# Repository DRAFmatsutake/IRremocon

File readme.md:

# 汎用リモコン送受信機
# 機能
- web経由で任意信号の送信
- web経由で任意信号の受信＆送信用数値へ変換
# 仕様
- esp32 devkit V1 を使用
- arduinoIDEで作成
- IRセンサ関係を行えるIRremoteLibraryの使用
- 送信信号は4bitを文字化したものを使用する
# 回路
- 電源はUSB給電を想定
- トランジスタhfeは250前後とする
- 赤外線LEDへの給電は瞬間電流を超えない程度の150mA前後で設計

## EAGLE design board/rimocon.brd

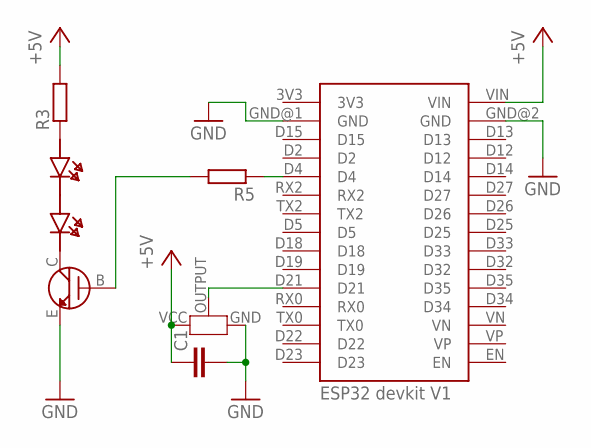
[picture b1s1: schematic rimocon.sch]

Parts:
C1: C-EU025-024X044; C025-024X044
R3, R5: R-EU_0204/5; 0204/5
U$1: 2SC1815; 1815
U$2: OSRB38C9AA; OSRB38
U$3: ESP32DEVKITV1
U$5, U$6: LEDOSI5FU3A11C; OSI5FU3A11C

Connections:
3V3: U$3.3V3
+5V: C1.1, R3.2, U$2.VCC, U$3.VIN
GND: C1.2, U$1.E, U$2.GND, U$3.GND@1 (GND), U$3.GND@2 (GND)
unnamed: U$1.C, U$5.K (CATHODE)
unnamed: R3.1, U$6.A (ANODE)
unnamed: R5.1, U$3.D4
unnamed: U$2.OUTPUT, U$3.D21
unnamed: R5.2, U$1.B
unnamed: U$5.A (ANODE), U$6.K (CATHODE)

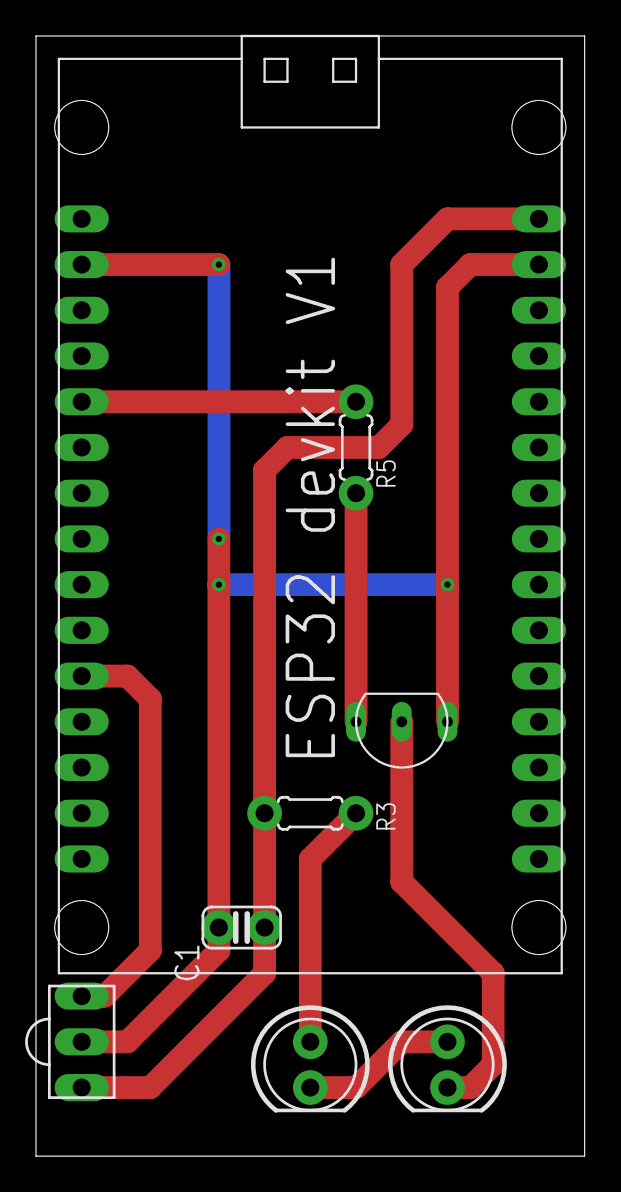
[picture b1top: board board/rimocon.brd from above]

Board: 2 copper layers, 30.5 x 62.2 mm, 8 parts (0 on the bottom side), 8 nets.

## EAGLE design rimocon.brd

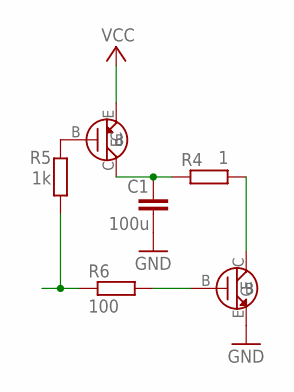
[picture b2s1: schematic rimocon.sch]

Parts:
C1: 100u; C025-025X050
R4: 1; 0204/5
R5: 1k; 0204/5
R6: 100; 0204/5
U$1: 2SC1815; 1815
U$2: 2SA1815; 1815

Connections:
GND: C1.2, U$1.E
unnamed: R5.2, U$2.B
unnamed: C1.1, R4.1, U$2.C
unnamed: R6.2, U$1.B
unnamed: R5.1, R6.1
unnamed: R4.2, U$1.C
VCC: U$2.E

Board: 2 copper layers, 6 parts (0 on the bottom side), 6 nets, no tracks yet.

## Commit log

2022-11-04 create brd
2022-11-06 受信処理の実装
2022-11-06 送信信号のチェクプログラム実装
2022-11-06 送受信表示の統合とそれに伴う回路修正
2022-11-07 回路をエミッタ設置へと変更 単ボタンリモコン用繰り返し処理の実装
2022-11-10 回路の修正
2023-03-07 信号の長いエアコン等用にバッファを拡張
